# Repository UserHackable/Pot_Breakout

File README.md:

## For Arduino 

I created this board to act as a mini shield to provide an easy way to have four analog adjustments on the Arduino with A0 through A3

It uses a common and inexpensive trim-pot form factor, but makes it much easier to connect them to the arduino. 

## PotBreakout 

### Board dimensions

* (130000, 50000) original units
* (1.3000, 0.5000) inches
* (33.0200, 12.7000) mm

| Front | Back |
| --- | --- |
|  |  |

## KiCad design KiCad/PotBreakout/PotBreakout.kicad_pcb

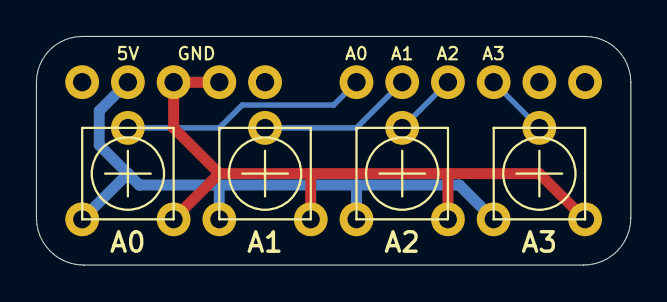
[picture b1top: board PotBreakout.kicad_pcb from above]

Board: 2 copper layers, 33.0 x 12.7 mm, 6 parts (0 on the bottom side), 6 nets.

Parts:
JP1: 1X06
JP2: 1X05_NO_SILK
R1, R2, R3, R4: TRIMPOTPTH; TRIM_POT_PTH

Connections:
5V: JP2.4, R1.1, R2.1, R3.1, R4.1
A0: JP1.6, R1.2
A1: JP1.5, R2.2
A2: JP1.4, R3.2
A3: JP1.3, R4.2
GND: JP2.2, JP2.3, R1.3, R2.3, R3.3, R4.3

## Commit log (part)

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2016-04-08 from Makefile
